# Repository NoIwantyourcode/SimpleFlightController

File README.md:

# Introduction
Hi!,

Welcome to my simple filght controller repository

This is a flight controller as the name suggests that is specifically designed to pilot remote controlled aircraft and provides accurate data to make flying your plane easier!,
some features I plan for to be included in the firmware are
       - 3 axis stabilization
       - altitude management

This is not a comprehensize list of features I may include and the actual firmware may have a lot more

Here are a few images of the Flight controller Schematics, PCB view and Rendered PCB view

# Schematics

# PCB view

# Rendered PCB View

# Display case (one screenshot is fitted with PCB)

NOTES TO REVIEWER:

I have had to substitute a few of components due to part shortfalls like the ICM-45686 had to substituted with the ICM-45605

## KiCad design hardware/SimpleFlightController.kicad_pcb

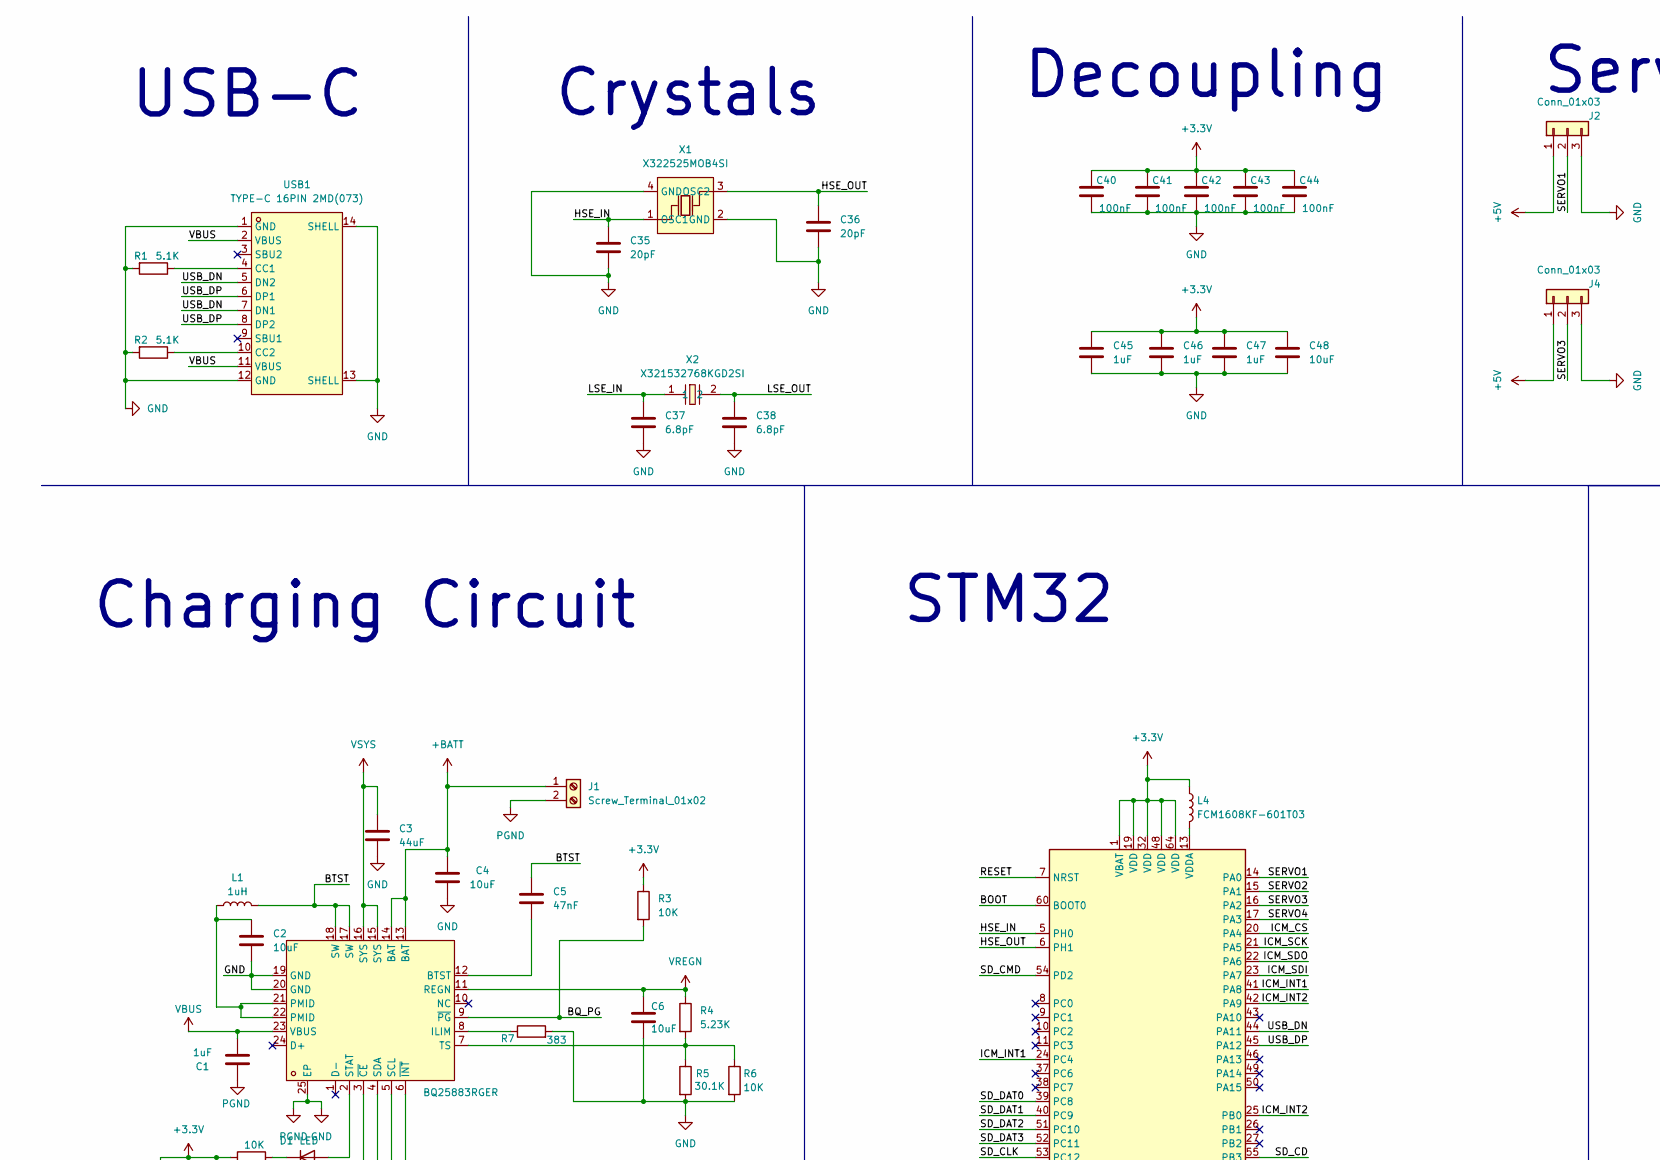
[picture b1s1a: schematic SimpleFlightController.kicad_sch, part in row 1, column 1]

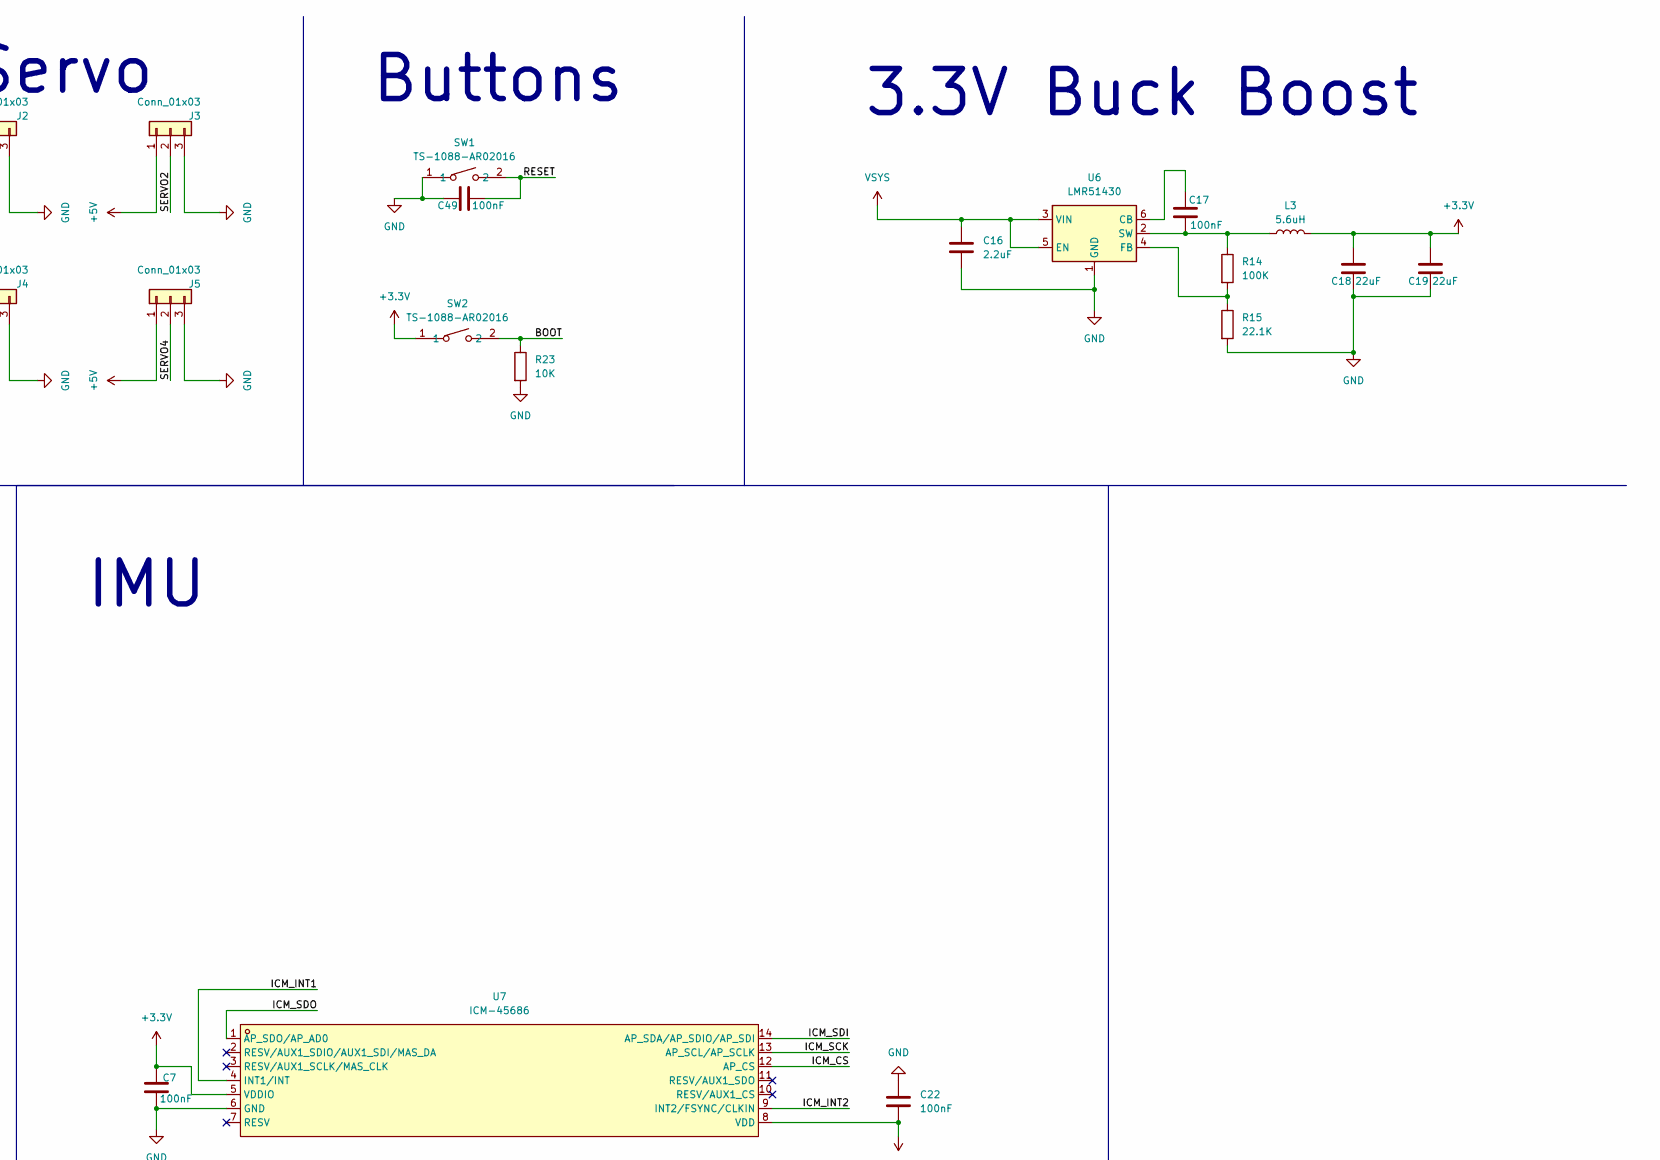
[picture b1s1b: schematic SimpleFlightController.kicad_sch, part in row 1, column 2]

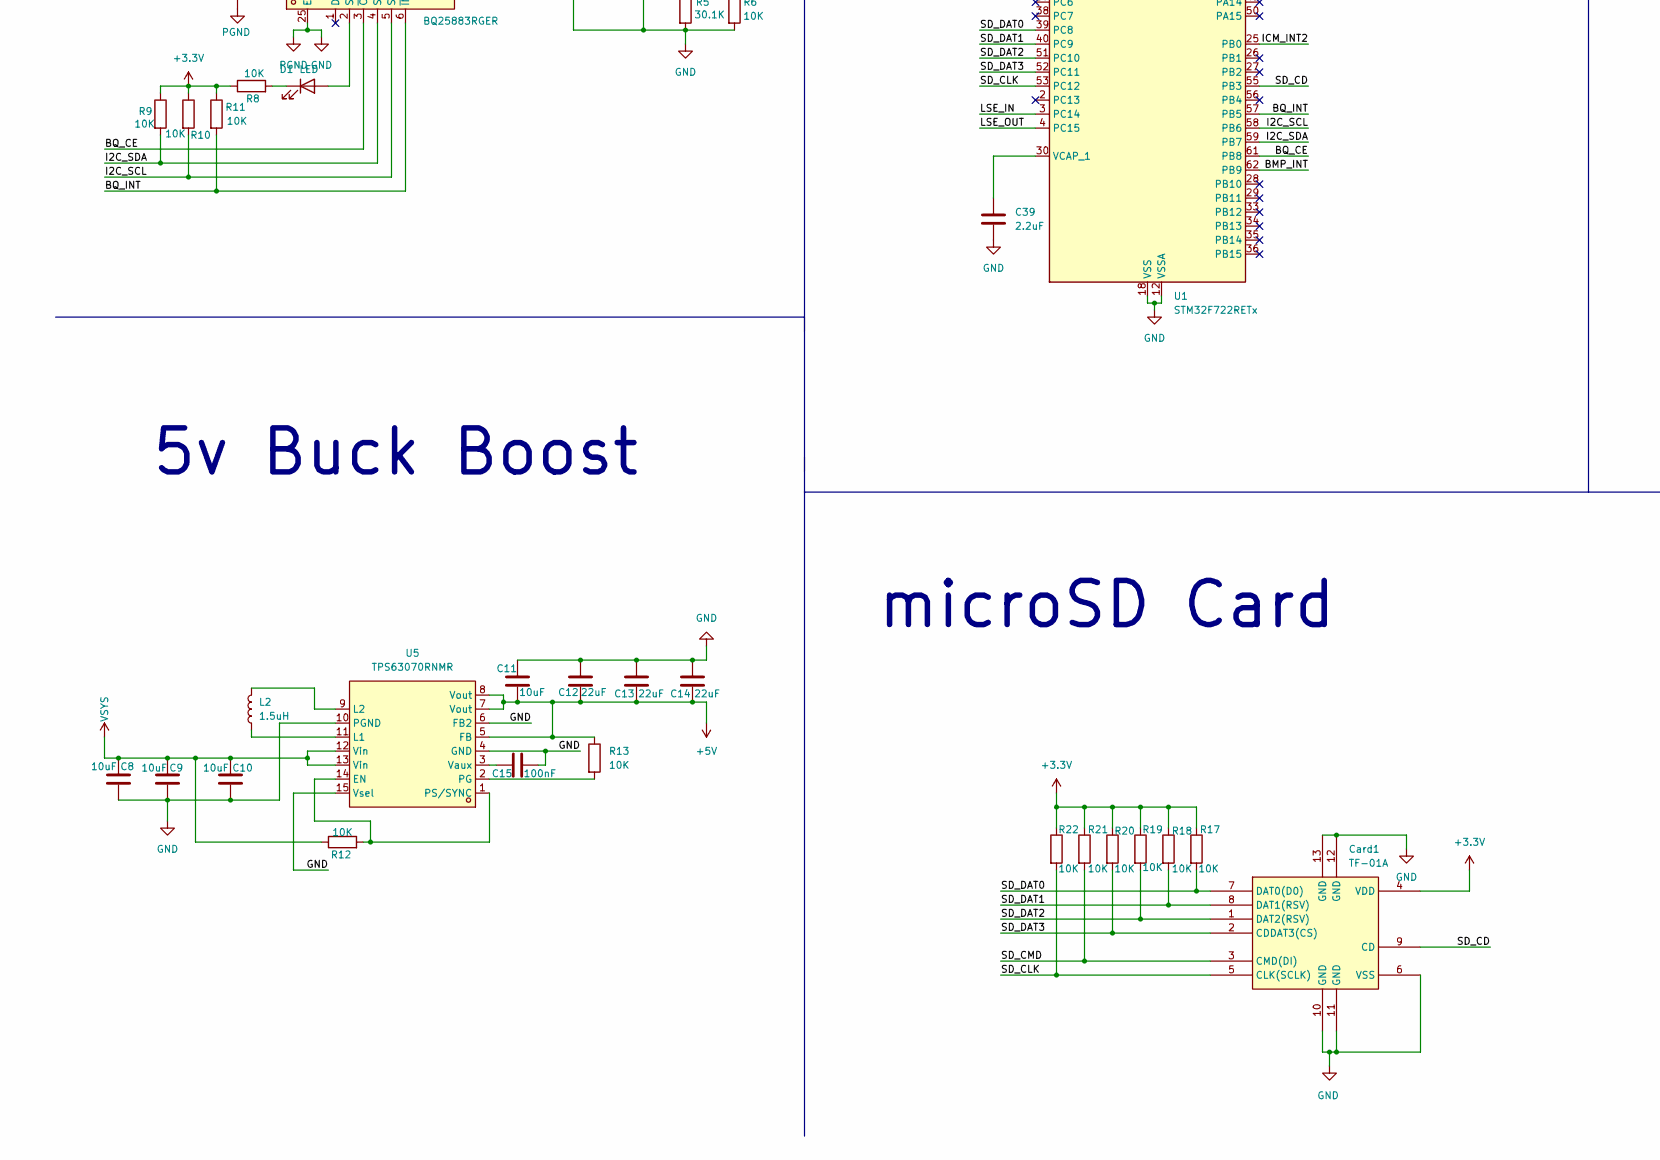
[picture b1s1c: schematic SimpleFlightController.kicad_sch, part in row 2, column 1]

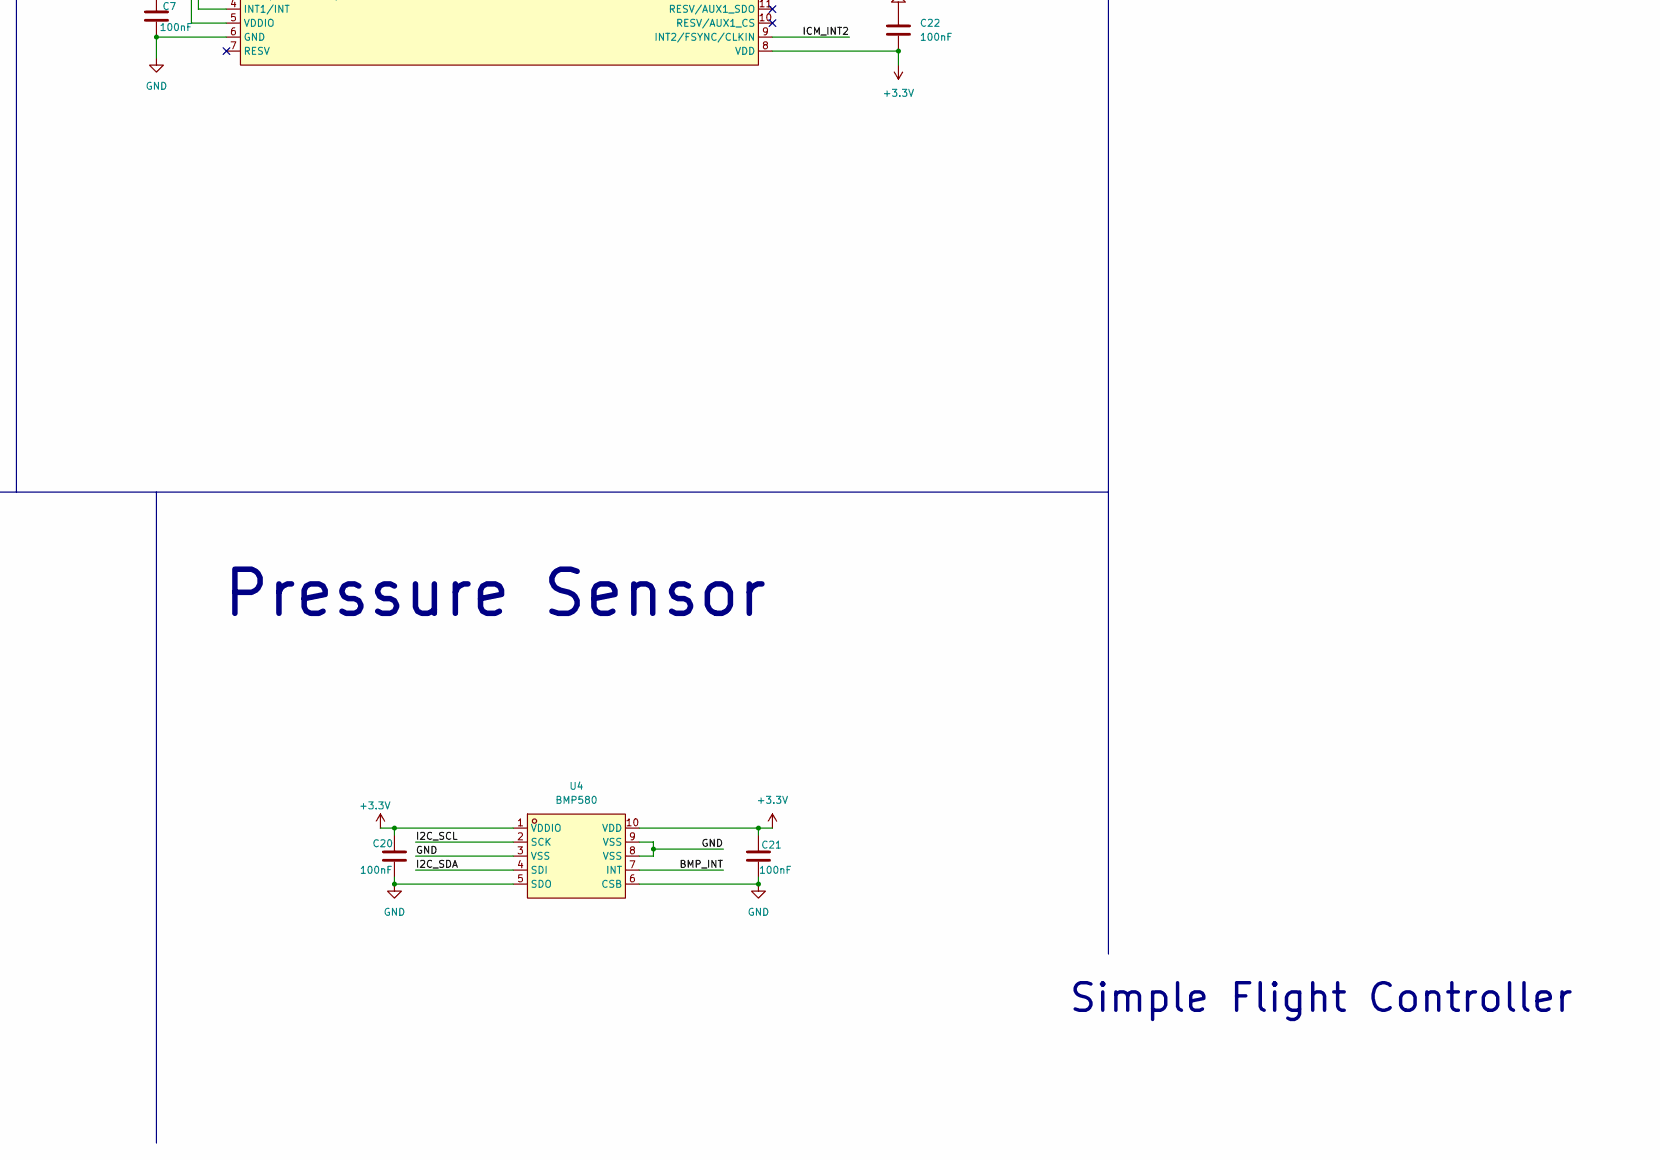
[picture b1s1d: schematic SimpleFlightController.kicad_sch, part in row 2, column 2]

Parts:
C1, C45, C46, C47: 1uF; C_0402_1005Metric
C2, C6, C48: 10uF; C_0402_1005Metric
C3: 44uF; C_0805_2012Metric
C4, C10, C11: 10uF; C_0603_1608Metric
C5: 47nF; C_0201_0603Metric
C7, C15, C17, C20, C21, C22, C40, C41, C42, C43, C44, C49: 100nF; C_0201_0603Metric
C8, C9: 10uF; C_0805_2012Metric
C12, C13, C14: 22uF; C_0805_2012Metric
C16: 2.2uF; C_0603_1608Metric
C18, C19: 22uF; C_0402_1005Metric
C35, C36: 20pF; C_0201_0603Metric
C37, C38: 6.8pF; C_0201_0603Metric
C39: 2.2uF; C_0201_0603Metric
Card1: TF-01A; TF-SMD_TF-01A; LCSC Part C91145
D1: LED; LED_0402_1005Metric
J1: Screw_Terminal_01x02; TerminalBlock_Xinya_XY308-2.54-2P_1x02_P2.54mm_Horizontal
J2, J3, J4, J5: Conn_01x03; PinHeader_1x03_P2.54mm_Vertical
L1: 1uH; L2520
L2: 1.5uH; IND-SMD_L4.0-W4.0-A
L3: 5.6uH; IND-SMD_L3.0-W3.0
L4: FCM1608KF-601T03; L0603
R1, R2: 5.1K; R_0201_0603Metric
R3, R6, R8, R9, R10, R11, R12, R13, R17, R18, R19, R20, R21, R22, R23: 10K; R_0201_0603Metric
R4: 5.23K; R_0201_0603Metric
R5: 30.1K; R_0201_0603Metric
R7: 383; R_0201_0603Metric
R14: 100K; R_0402_1005Metric
R15: 22.1K; R_0201_0603Metric
SW1, SW2: TS-1088-AR02016; SW-SMD_L3.9-W3.0-P4.45; LCSC Part C720477
U1: STM32F722RETx; LQFP-64_10x10mm_P0.5mm
U2: BQ25883RGER; VFQFPN-24_L4.0-W4.0-P0.50-BL-EP2.8; LCSC Part C544362
U4: BMP580; LGA-10_L2.0-W2.0-P0.50-TL_BMP580; LCSC Part C22391138
U5: TPS63070RNMR; VQFN-HR-15_L3.0-W2.5-P0.50-BL_TPS63070RNMR; LCSC Part C109322
U6: LMR51430; SOT-23-6
U7: ICM-45686; LGA-14_L3.0-W2.5-P0.50-TL; LCSC Part C22459454
USB1: TYPE-C 16PIN 2MD(073); USB-C-SMD_TYPE-C-6PIN-2MD-073; LCSC Part C2765186
X1: X322525MOB4SI; CRYSTAL-SMD_4P-L3.2-W2.5-BL; LCSC Part C9006
X2: X321532768KGD2SI; OSC-SMD_L3.2-W1.5; LCSC Part C620155

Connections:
+3.3V: C7.1, C18.2, C19.2, C20.1, C21.2, C22.2, C40.1, C41.1, C42.1, C43.1, C44.1, C45.1, C46.1, C47.1, C48.1, Card1.4 (VDD), L3.2, L4.1, R3.1, R8.1, R9.1, R10.1, R11.1, R17.1, R18.1, R19.1, R20.1, R21.1, R22.1, SW2.1, U1.1 (VBAT), U1.19 (VDD), U1.32 (VDD), U1.48 (VDD), U1.64 (VDD), U4.1 (VDDIO), U4.10 (VDD), U7.5 (VDDIO), U7.8 (VDD)
+5V: C11.1, C12.1, C13.1, C14.1, J2.1, J3.1, J4.1, J5.1, R13.1, U5.5 (FB), U5.7 (Vout), U5.8 (Vout)
+BATT: C4.1, J1.1, U2.13 (BAT), U2.14 (BAT)
/BMP_INT: U1.62 (PB9), U4.7 (INT)
/BOOT: R23.1, SW2.2, U1.60 (BOOT0)
/BQ_CE: U1.61 (PB8), U2.3 (~CE)
/BQ_INT: R11.2, U1.57 (PB5), U2.6 (~INT)
/BQ_PG: R3.2, U2.9 (~PG)
/BTST: C5.1, L1.2, U2.17 (SW), U2.18 (SW)
/HSE_IN: C35.1, U1.5 (PH0), X1.1 (OSC1)
/HSE_OUT: C36.1, U1.6 (PH1), X1.3 (OSC2)
/I2C_SCL: R10.2, U1.58 (PB6), U2.5 (SCL), U4.2 (SCK)
/I2C_SDA: R9.2, U1.59 (PB7), U2.4 (SDA), U4.4 (SDI)
/ICM_CS: U1.20 (PA4), U7.12 (AP_CS)
/ICM_INT1: U1.24 (PC4), U1.41 (PA8), U7.4 (INT1/INT)
/ICM_INT2: U1.25 (PB0), U1.42 (PA9), U7.9 (INT2/FSYNC/CLKIN)
/ICM_SCK: U1.21 (PA5), U7.13 (AP_SCL/AP_SCLK)
/ICM_SDI: U1.23 (PA7), U7.14 (AP_SDA/AP_SDIO/AP_SDI)
/ICM_SDO: U1.22 (PA6), U7.1 (AP_SDO/AP_AD0)
/LSE_IN: C37.1, U1.3 (PC14), X2.1
/LSE_OUT: C38.1, U1.4 (PC15), X2.2
/RESET: C49.1, SW1.2, U1.7 (NRST)
/SD_CD: Card1.9 (CD), U1.55 (PB3)
/SD_CLK: Card1.5 (CLK(SCLK)), R22.2, U1.53 (PC12)
/SD_CMD: Card1.3 (CMD(DI)), R21.2, U1.54 (PD2)
/SD_DAT0: Card1.7 (DAT0(D0)), R17.2, U1.39 (PC8)
/SD_DAT1: Card1.8 (DAT1(RSV)), R18.2, U1.40 (PC9)
/SD_DAT2: Card1.1 (DAT2(RSV)), R19.2, U1.51 (PC10)
/SD_DAT3: Card1.2 (CDDAT3(CS)), R20.2, U1.52 (PC11)
/SERVO1: J2.2, U1.14 (PA0)
/SERVO2: J3.2, U1.15 (PA1)
/USB_DN: U1.44 (PA11), USB1.5 (DN2), USB1.7 (DN1)
/USB_DP: U1.45 (PA12), USB1.6 (DP1), USB1.8 (DP2)
GND: C1.1, C2.2, C3.2, C4.2, C6.2, C7.2, C8.2, C9.2, C10.2, C11.2, C12.2, C13.2, C14.2, C15.2, C16.2, C18.1, C19.1, C20.2, C21.1, C22.1, C35.2, C36.2, C37.2, C38.2, C39.2, C40.2, C41.2, C42.2, C43.2, C44.2, C45.2, C46.2, C47.2, C48.2, C49.2, Card1.6 (VSS), Card1.10 (GND), Card1.11 (GND), Card1.12 (GND), Card1.13 (GND), J1.2, J2.3, J3.3, J4.3, J5.3, R1.2, R2.2, R5.2, R6.2, R7.2, R15.2, R23.2, SW1.1, U1.12 (VSSA), U1.18 (VSS), U1.31 (VSS), U1.47 (VSS), U1.63 (VSS), U2.19 (GND), U2.20 (GND), U2.25 (EP), U4.3 (VSS), U4.5 (SDO), U4.6 (CSB), U4.8 (VSS), U4.9 (VSS), U5.4 (GND), U5.6 (FB2), U5.10 (PGND), U5.15 (Vsel), U6.1 (GND), U7.6 (GND), USB1.1 (GND), USB1.12 (GND), USB1.13 (SHELL), USB1.14 (SHELL), X1.2 (GND), X1.4 (GND)
unnamed: C2.1, L1.1, U2.21 (PMID), U2.22 (PMID)
unnamed: D1.2 (A), U2.2 (STAT)
unnamed: D1.1 (K), R8.2
unnamed: J4.2, U1.16 (PA2)
unnamed: J5.2, U1.17 (PA3)
unnamed: C39.1, U1.30 (VCAP_1)
unnamed: L4.2, U1.13 (VDDA)
unnamed: C5.2, U2.12 (BTST)
unnamed: R7.1, U2.8 (ILIM)
unnamed: R4.2, R5.1, R6.1, U2.7 (TS)
unnamed: R12.2, U5.1 (PS/SYNC), U5.14 (EN)
unnamed: L2.1, U5.11 (L1)
unnamed: L2.2, U5.9 (L2)
unnamed: R13.2, U5.2 (PG)
unnamed: C15.1, U5.3 (Vaux)
unnamed: C17.1, U6.6 (CB)
unnamed: R14.2, R15.1, U6.4 (FB)
unnamed: C17.2, L3.1, R14.1, U6.2 (SW)
unnamed: R1.1, USB1.4 (CC1)
unnamed: R2.1, USB1.10 (CC2)
VBUS: C1.2, U2.23 (VBUS), USB1.2 (VBUS), USB1.11 (VBUS)
VREGN: C6.1, R4.1, U2.11 (REGN)
VSYS: C3.1, C8.1, C9.1, C10.1, C16.1, R12.1, U2.15 (SYS), U2.16 (SYS), U5.12 (Vin), U5.13 (Vin), U6.3 (VIN), U6.5 (EN)

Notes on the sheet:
STM32
Crystals
Simple Flight Controller
3.3V Buck Boost
Buttons
Charging Circuit
USB-C
Decoupling
Servo
Pressure Sensor
5v Buck Boost
microSD Card
IMU

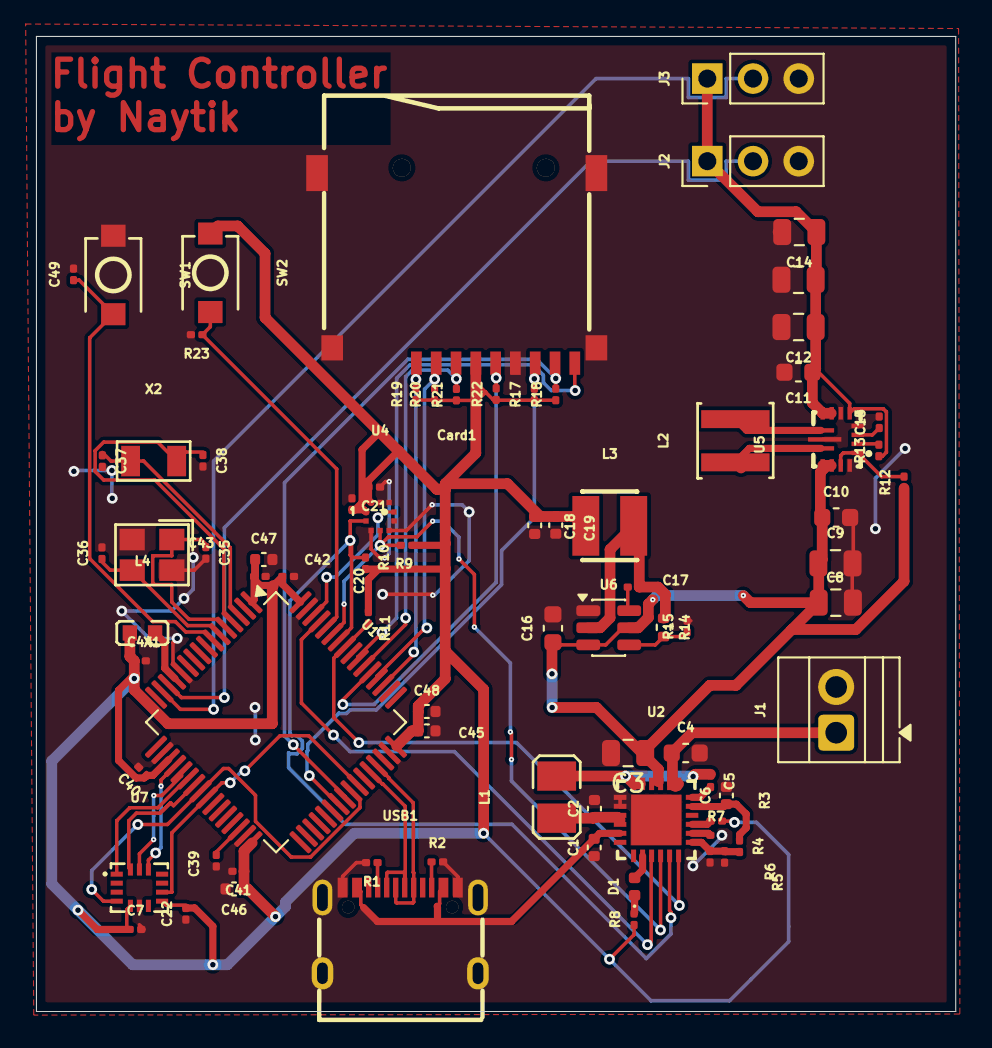
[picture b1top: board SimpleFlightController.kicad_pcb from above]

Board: 2 copper layers, 51.1 x 54.2 mm, 79 parts (0 on the bottom side), 55 nets.

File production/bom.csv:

Designator,Footprint,Quantity,Value,LCSC Part #
"C1, C45, C46, C47",0402,4,1uF,
"C10, C11, C4",0603,3,10uF,
"C12, C13, C14",0805,3,22uF,
"C15, C17, C20, C21, C22, C40, C41, C42, C43, C44, C49, C7",0201,12,100nF,
C16,0603,1,2.2uF,
"C18, C19",0402,2,22uF,
"C2, C48, C6",0402,3,10uF,
C3,0805,1,44uF,
"C35, C36",0201,2,20pF,
"C37, C38",0201,2,6.8pF,
C39,0201,1,2.2uF,
C5,0201,1,47nF,
"C8, C9",0805,2,10uF,
CARD1,TF-SMD_TF-01A,1,TF-01A,C91145
D1,0402,1,LED,
J1,TerminalBlock_Xinya_XY308-2.54-2P_1x02_P2.54mm_Horizontal,1,Screw_Terminal_01x02,
"J2, J3",PinHeader_1x03_P2.54mm_Vertical,2,Conn_01x03,
L1,L2520,1,1uH,
L2,IND-SMD_L4.0-W4.0-A,1,1.5uH,
L3,IND-SMD_L3.0-W3.0,1,5.6uH,
L4,L0603,1,FCM1608KF-601T03,
"R1, R2",0201,2,5.1K,
"R10, R11, R12, R13, R17, R18, R19, R20, R21, R22, R23, R3, R6, R8, R9",0201,15,10K,
R14,0402,1,100K,
R15,0201,1,22.1K,
R4,0201,1,5.23K,
R5,0201,1,30.1K,
R7,0201,1,383,
"SW1, SW2",SW-SMD_L3.9-W3.0-P4.45,2,TS-1088-AR02016,C720477
U1,LQFP-64_10x10mm_P0.5mm,1,STM32F722RETx,
U2,VFQFPN-24_L4.0-W4.0-P0.50-BL-EP2.8,1,BQ25883RGER,C544362
U4,LGA-10_L2.0-W2.0-P0.50-TL_BMP580,1,BMP580,C22391138
U5,VQFN-HR-15_L3.0-W2.5-P0.50-BL_TPS63070RNMR,1,TPS63070RNMR,C109322
U6,SOT-23-6,1,LMR51430,
U7,LGA-14_L3.0-W2.5-P0.50-TL,1,ICM-45686,C22459454
USB1,USB-C-SMD_TYPE-C-6PIN-2MD-073,1,TYPE-C 16PIN 2MD(073),C2765186
X1,CRYSTAL-SMD_4P-L3.2-W2.5-BL,1,X322525MOB4SI,C9006
X2,OSC-SMD_L3.2-W1.5,1,X321532768KGD2SI,C620155

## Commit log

2025-12-15 These are the design files for the flight controller
2025-12-15 Create del
2025-12-15 KiCAD design file for the Flight Controller
2025-12-16 Create x
2025-12-16 Production files for PCBA
    Includes BOM (Bill of Materials), Component positioning files for PCB assembly and Gerber file for the board itself
2025-12-16 firmware for the controller, uses Arduino IDE
2025-12-17 added firmware
2025-12-23 New BOM provided by JLCPCB
2025-12-23 Added new BOM by JLCPCB
2025-12-23 Updated BOM
2025-12-23 Updated BOM.csv
2025-12-25 Other Costs for the use of PCBA in the project
2025-12-25 Update README.md
    Added more notes to reviewers
2026-01-07 added project design files
2026-01-07 added Bill of Materials
2026-01-07 added production files
2026-02-18 added cad file and source file
